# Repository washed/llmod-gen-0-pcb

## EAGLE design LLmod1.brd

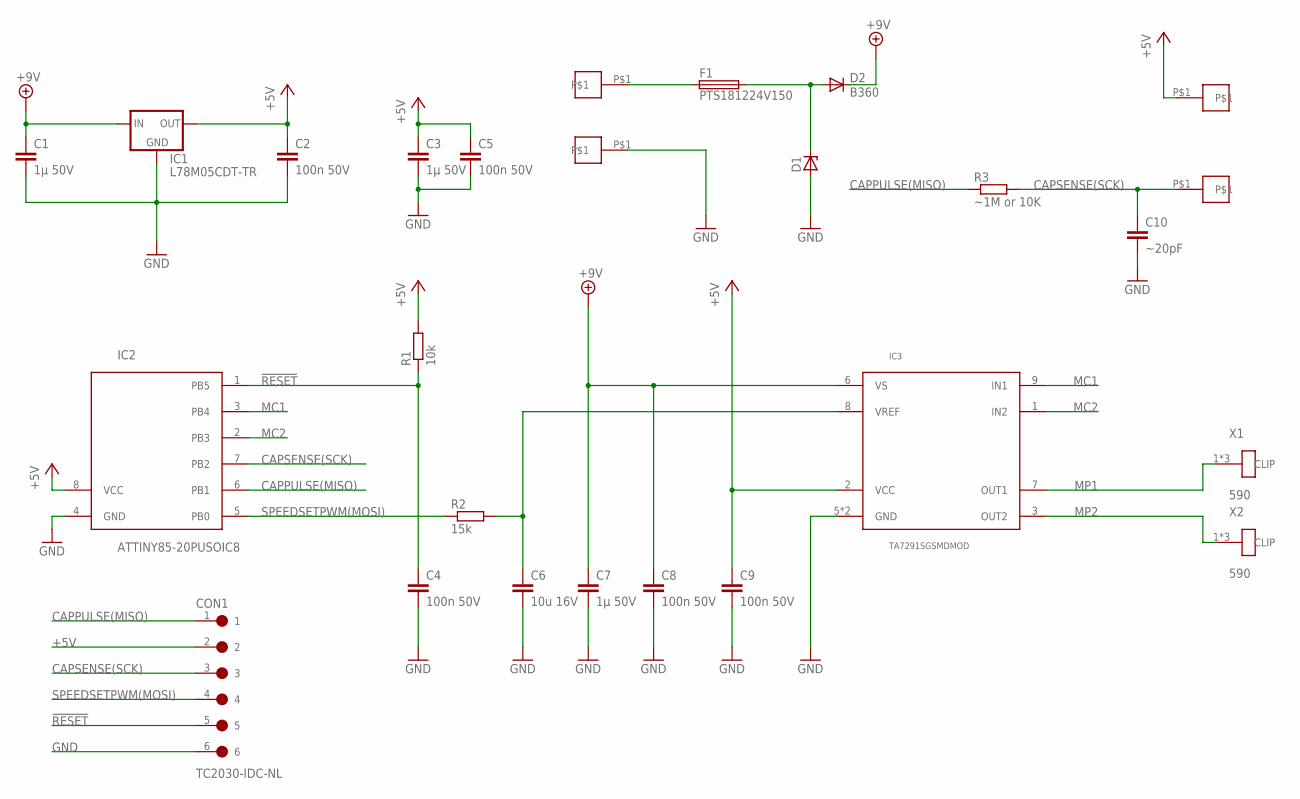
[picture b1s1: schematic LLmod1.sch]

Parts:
+5V: SOLPADSMALLMILL; SINGLE-PAD-MED-SMALLMILL
BTN: SOLPADSMALLMILL; SINGLE-PAD-MED-SMALLMILL
C1, C3, C7: 1µ 50V; C0805
C2, C4, C5, C8, C9: 100n 50V; C0402
C6: 10u 16V; C0805
C10: ~20pF; C0402
CON1: TC2030-IDC-NL
D1: ZENER-DIODESMB; SMB
D2: B360; DO214AA
F1: PTS181224V150; 1812
GND: SOLPAD; SINGLE-PAD-MED
IC1: L78M05CDT-TR; DPAK
IC2: ATTINY85-20PUSOIC8; SOIC-8-5,3MM
IC3: TA7291SGSMDMOD; SIP9-SMDMOD
R1: 10k; R0402
R2: 15k; R0402
R3: ~1M or 10K; R0402
VBAT: SOLPAD; SINGLE-PAD-MED
X1, X2: 590; 590K

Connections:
!RESET: C4.1, CON1.5, IC2.1 (PB5), R1.1
+5V: +5V.P$1, C2.1, C3.1, C5.1, C9.1, CON1.2, IC1.P$3 (OUT), IC2.8 (VCC), IC3.2 (VCC), R1.2
+9V: C1.1, C7.1, C8.1, D2.C, IC1.P$2 (IN), IC3.6 (VS)
CAPPULSE(MISO): CON1.1, IC2.6 (PB1), R3.1
CAPSENSE(SCK): BTN.P$1, C10.1, CON1.3, IC2.7 (PB2), R3.2
GND: C1.2, C2.2, C3.2, C4.2, C5.2, C6.2, C7.2, C8.2, C9.2, C10.2, CON1.6, D1.A, GND.P$1, IC1.P$1 (GND), IC2.4 (GND), IC3.5 (GND), IC3.THERMAL (GND)
MC1: IC2.3 (PB4), IC3.9 (IN1)
MC2: IC2.2 (PB3), IC3.1 (IN2)
MP1: IC3.7 (OUT1), X1.1, X1.2, X1.3
MP2: IC3.3 (OUT2), X2.1, X2.2, X2.3
unnamed: C6.1, IC3.8 (VREF), R2.2
unnamed: F1.1, VBAT.P$1
unnamed: D1.C, D2.A, F1.2
SPEEDSETPWM(MOSI): CON1.4, IC2.5 (PB0), R2.1

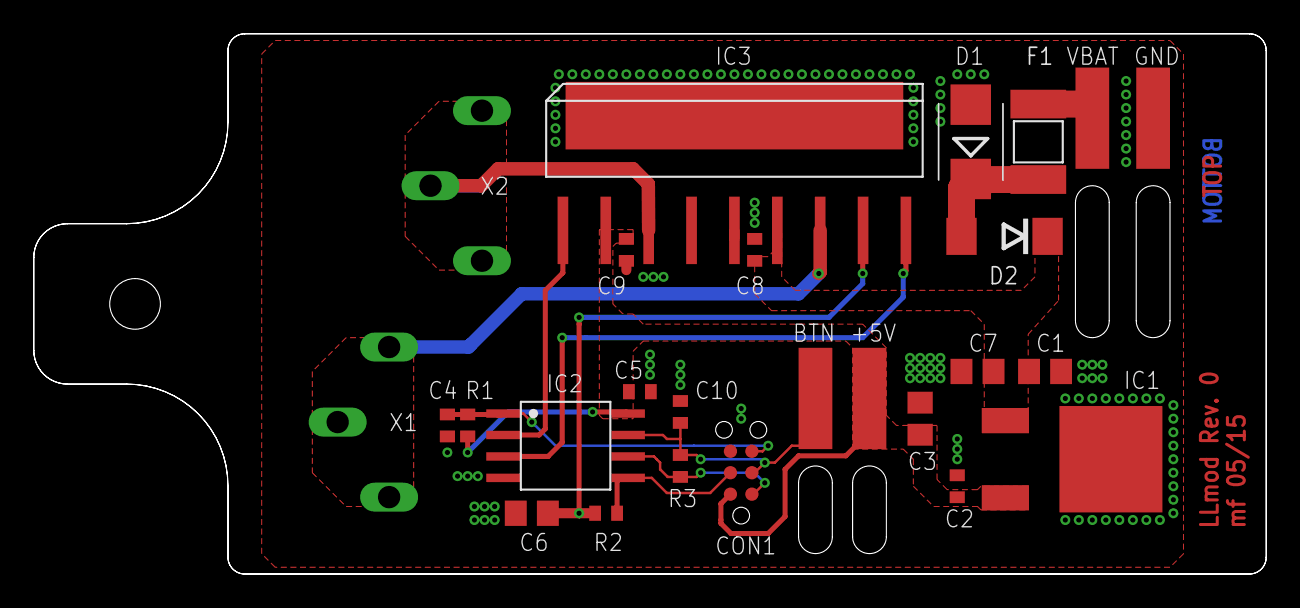
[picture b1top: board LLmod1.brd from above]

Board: 2 copper layers, 73.0 x 32.0 mm, 26 parts (0 on the bottom side), 14 nets.

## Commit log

2015-10-25 Initial commit.
